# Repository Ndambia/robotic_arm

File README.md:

# robotic_arm
A six degree pick and place robotic arm for the packaging and assembly industry

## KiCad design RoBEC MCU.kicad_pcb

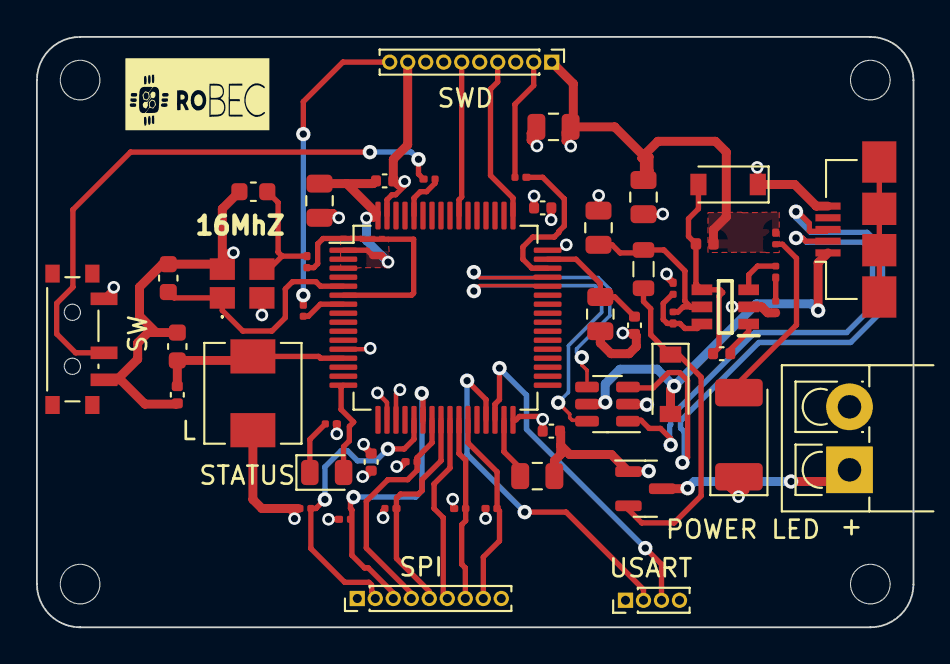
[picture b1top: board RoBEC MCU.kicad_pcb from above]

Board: 4 copper layers, 48.7 x 32.8 mm, 54 parts (0 on the bottom side), 41 nets.

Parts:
16MhZ: 16MHz; ECS3225MV160BNTR3
C1: 4u7; C_0805_2012Metric
C2, C5: 12p; C_0603_1608Metric
C3, C6, C9, C11: 100n; C_0402_1005Metric
C4: 1n; C_0603_1608Metric
C7, C15: 10n; C_0402_1005Metric
C8, C10, C16: 10u; C_0805_2012Metric
C12, C13: 2u2; C_0805_2012Metric
C14: 2u2; C_0402_1005Metric
D1, D3: B5819W; D_SOD-123
FB1: 600 @ 600MHz; L_0805_2012Metric
H1, H2, H3, H4: MountingHole_Pad; MountingHole_2.2mm_M2_DIN965
J1: ST_01x02; TerminalBlock_4Ucon_1x02_P3.50mm_Vertical
J2: USB_B_Micro; USB_Micro-B_Amphenol_10104110_Horizontal
L: 39n; L_Sunlord_MWSA0518_5.4x5.2mm
L2: 10u; L_0402_1005Metric
POWER LED: LED; LED_2010_5025Metric_Pad1.52x2.65mm_HandSolder
Q1: AO3400A; SOT-23
R1: 10k; R_0201_0603Metric
R2: 47; R_0201_0603Metric
R3: 1k5; R_0201_0603Metric
R4, R5, R8, R9, R10, R12: 20; R_0201_0603Metric
R6: 87k; R_0201_0603Metric
R7: 64k; R_0201_0603Metric
R14: 15k; R_0201_0603Metric
R15: 270; R_0201_0603Metric
R16, R17: 22; R_0201_0603Metric
R18: 1k; R_0201_0603Metric
SPI: Conn_01x05; PinHeader_1x09_P1.00mm_Vertical
STATUS: LED; LED_0805_2012Metric
SW: SW_SPDT; SW_SPDT_PCM12
SWD: Conn_02x05; PinHeader_1x10_P1.00mm_Vertical
U1: STM32F405RGT6; LQFP-64_10x10mm_P0.5mm
U2: MP2359DJ
U3: USBLC6-2SC6; SOT-23-6
USART: Conn_01x04; PinHeader_1x04_P1.00mm_Vertical

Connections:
+3.3VA: C4.1, C7.1, L.2, U1.13 (VDDA)
+3V3: C1.1, C3.1, C6.1, C8.2, C9.1, C10.2, C11.1, L.1, L2.2, R4.1, R5.1, R8.1, R9.1, R10.1, R12.1, R18.1, SPI.1, SW.1 (A), SWD.1, U1.1 (VBAT), U1.19 (VDD), U1.32 (VDD), U1.48 (VDD), U1.64 (VDD), USART.1
+5V: D3.2 (A), J2.1 (VBUS), U3.5 (VBUS)
+12V: J1.1, Q1.3 (D)
BOOT0: R1.2, U1.60 (BOOT0)
BS: C15.1, U2.1 (BS)
CS1: R12.2, SPI.5, U1.24 (PC4)
CS2: SPI.6, U1.25 (PC5)
CS3: R10.2, SPI.7, U1.26 (PB0)
CS4: R9.2, SPI.8, U1.27 (PB1)
EN: R6.2, R7.1, U2.6 (EN)
FB: R14.1, U2.3 (FB)
GND: 16MhZ.2, 16MhZ.4, C1.2, C2.2, C3.2, C4.2, C5.2, C6.2, C7.2, C8.1, C9.2, C10.1, C11.2, C12.2, C13.2, C14.2, C16.2, D1.1 (K), J1.2, J2.5 (GND), POWER LED.1 (K), Q1.1 (G), R3.2, R7.2, R15.2, SPI.9, SW.3 (C), SWD.3, SWD.5, SWD.9, U1.12 (VSSA), U1.18 (VSS), U1.63 (VSS), U2.2 (GND), U3.2 (GND), USART.4
HSE_IN: 16MhZ.1, C2.1, U1.5 (PH0)
HSE_OUT: R2.1, U1.6 (PH1)
IN: C16.1, FB1.2, R6.1, U2.5 (IN)
LED_STATUS: STATUS.2 (A), U1.16 (PA2)
NRST: R17.2, U1.7 (NRST)
unnamed: 16MhZ.3, C5.1, R2.2
unnamed: C12.1, U1.31 (VCAP_1)
unnamed: C13.1, C14.1, U1.47 (VCAP_2)
unnamed: R3.1, STATUS.1 (K)
unnamed: D3.1 (K), FB1.1, Q1.2 (S)
unnamed: POWER LED.2 (A), R18.2
unnamed: R16.1, SWD.2
unnamed: R17.1, SWD.10
unnamed: R1.1, SW.2 (B)
unnamed: R14.2, R15.1
SPI_MISO: R5.2, SPI.3, U1.22 (PA6)
SPI_MOSI: R4.2, SPI.4, U1.23 (PA7)
SPI_SCK: R8.2, SPI.2, U1.21 (PA5)
SW: C15.2, D1.2 (A), L2.1, U2.4 (SW)
SWCLK: SWD.4, U1.49 (PA14)
SWDIO: R16.2, U1.46 (PA13)
SWO: SWD.6, U1.55 (PB3)
USART_RX: U1.30 (PB11), USART.3
USART_TX: U1.29 (PB10), USART.2
USB_CONN_D+: J2.3 (D+), U3.3 (I/O2)
USB_CONN_D-: J2.2 (D-), U3.1 (I/O1)
USB_D+: U1.45 (PA12), U3.4 (I/O2)
USB_D-: U1.44 (PA11), U3.6 (I/O1)

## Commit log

2022-11-18 MCU files added
2022-11-18 pcb and sch files renamed
2022-11-18 Manufactering files renamed
2024-02-14 Create Matlab Simulation
    Octave environment was used to achieve the trajectory
